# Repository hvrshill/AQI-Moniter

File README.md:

# AQI-Moniter-
AQI Moniter Using ESP8266 and MQ - 9 sensor

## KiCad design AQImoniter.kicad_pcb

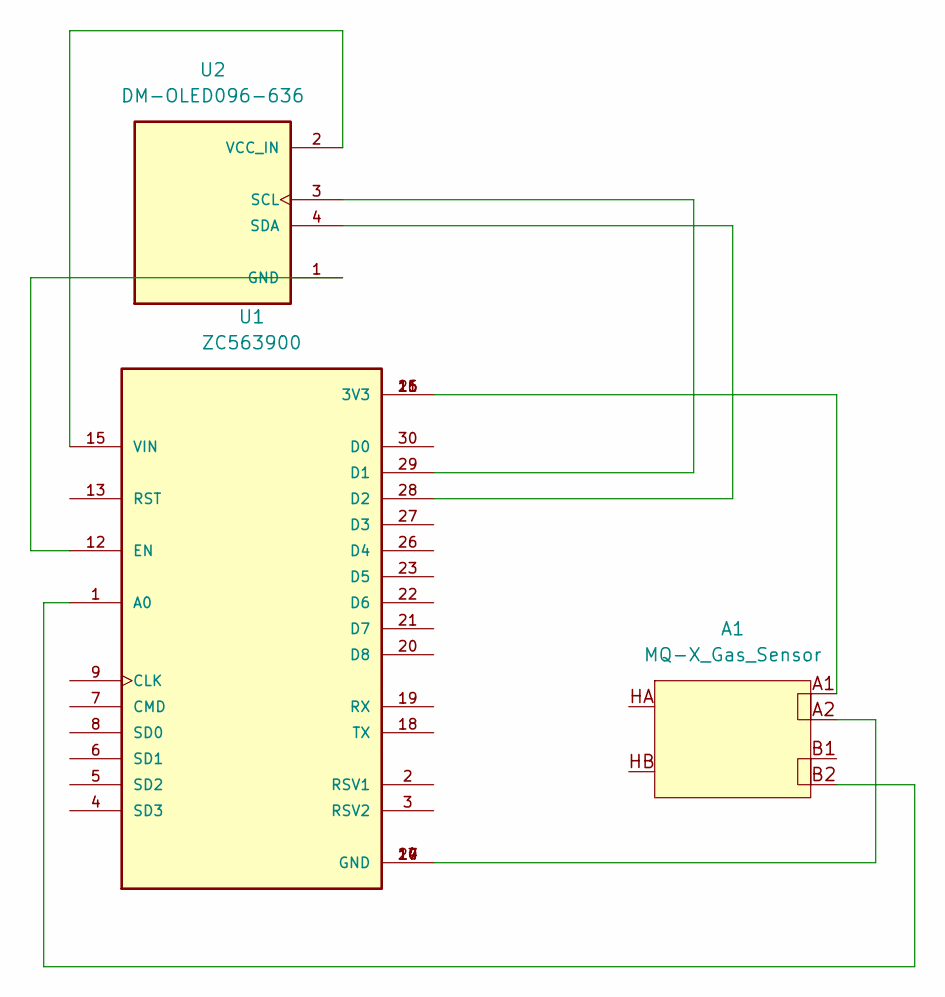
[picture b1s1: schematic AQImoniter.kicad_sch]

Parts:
A1: MQ-X_Gas_Sensor
U1: ZC563900; MODULE_ZC563900; PARTREV 1.0
U2: DM-OLED096-636; MODULE_DM-OLED096-636; PARTREV 2018-09-10

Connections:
unnamed: A1.A1, U1.11 (3V3), U1.16 (3V3), U1.25 (3V3)
unnamed: A1.A2, U1.10 (GND), U1.14 (GND), U1.17 (GND), U1.24 (GND)
unnamed: A1.B2, U1.1 (A0)
unnamed: U1.29 (D1), U2.3 (SCL)
unnamed: U1.28 (D2), U2.4 (SDA)
unnamed: U1.12 (EN), U2.1 (GND)
unnamed: U1.15 (VIN), U2.2 (VCC_IN)

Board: 2 copper layers, 3 parts (0 on the bottom side), 7 nets, no tracks yet.

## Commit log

2025-04-15 Added KiCadFiles
2025-04-15 Added footprints and symbols folder in assets
